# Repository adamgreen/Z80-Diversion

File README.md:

# Z80 Diversion

This project is a [Z80](https://www.zilog.com/index.php?option=com_product&Itemid=26&task=docs&businessLine=&parent_id=139&familyId=20&productId=Z84C00) based single board computer. A [RP2040 microcontroller](https://www.raspberrypi.com/documentation/microcontrollers/rp2040.html) is also included on the board. It is connected to the Z80 bus to:
* Provide the Z80 access to 64k of its 264k of SRAM.
* Allow a [Z80 compatible version of GDB](https://github.com/b-s-a/binutils-gdb) to debug the Z80 over a USB serial connection. The RP2040 is used as a hardware debugger for the Z80 much like modern JTAG or SWD probes (ie. Segger J-Link).

## Project Purpose
I want to verify some unit tests which exercise all of the instructions supported by the Z80 microprocessor. These tests can be used to verify Z80 emulation. Having the ability to also runs these tests against real Z80 hardware is desireable as it allows verifying the quality of the tests themselves. A few years ago, I did something similar for the ARMv6-M instruction tests that I wrote for my [pinkySim project](https://github.com/adamgreen/pinkySim).

## Project Progression
* The Z80, RP2040 Pico, and SN74HC165 shift register devices arrived from Digikey.
* I completed the initial schematic in KiCAD.
* I wired up an initial test version on my breadboard.
* I wrote simple proof of concept PIO and ARM code for the RP2040 to verify my hardware setup.
* I completed the initial PCB design in KiCAD.
* I ordered and received PCBs from [OSHPark](https://oshpark.com).
* I was able to download a [Z80 port of binutils/GDB](https://github.com/b-s-a/binutils-gdb) and build it on my Mac.
* I soldered up one of the PCBs and successfully tested it out with the code that I had previously developed.
* I simplified the PIO state machine code and got it running faster:
  * Can run the Z80 at 500kHz without requiring any wait cycles.
  * Can run the Z80 at faster clock rates (at least 5MHz) reliably but requires wait cycles as the RP2040 takes time to wait for the shift registers and respond to memory read/write requests.
* My [MRI core](https://github.com/adamgreen/mri) has been extended to handle debug targets which aren't just 32-bit. This will allow 64-bit in the future and 16-bit for Z80 debugging.
* The Z80 version of GDB is now able connect to the board via a RP2040 USB based serial connection to:
  * Examine and modify the Z80's 64k of RAM (which is actually a 64k global buffer on the RP2040).
  * Examine and modify the Z80's registers.
  * Single step the Z80.
  * Set up to 4 Code Breakpoints.
  * Set up to 2 Data Watchpoints
  * Z80 reset from GDB.

## Reading List
<br>
It has been around a decade since I last looked at the Z80 so I had to skim through a few Z80 references to refresh my memory of what it takes to interface this little guy to the outside world. These references included:
* [Build Your Own Z80 Computer by Steve Ciarcia](https://en.wikipedia.org/wiki/Build_Your_Own_Z80_Computer) ([Free PDF](http://www.pestingers.net/pdfs/other-computers/build-your-own-z80.pdf)).
* [Z80 CPU User Manual](https://www.zilog.com/docs/z80/UM0080.pdf)
* [Z80 Product Specification](https://www.zilog.com/docs/z80/ps0178.pdf)
* [Other Official Z80 Documents](https://www.zilog.com/index.php?option=com_product&Itemid=26&task=docs&businessLine=1&parent_id=139&familyId=20&productId=Z84C00)

I also skimmed some RP2040 documentation again as well to make sure that I had a good chance of successfully interfacing it to the Z80 before going too far down that path:
* [Raspberry Pi Pico Datasheet](https://datasheets.raspberrypi.com/pico/pico-datasheet.pdf)
* [RP2040 Datasheet](https://datasheets.raspberrypi.com/rp2040/rp2040-datasheet.pdf)

## High Level BOM
This board includes:
* A **Z80 Microprocessor** - I am using a [Z84C0020PEG](https://www.digikey.com/en/products/detail/zilog/Z84C0020PEG/928994) device since it is:
  * 20 MHz capable. I picked the fastest CMOS version of the device available. It can run at 20MHz when powered by a 5V supply but it should be able to run at a lower 3.3V (same as the RP2040) when clocked at lower frequencies (between 1 and 2.5 MHz).
  * 40-pin DIP package. Currently Digikey only has the DIP version of the 20MHz capable part in stock. I would have preferred the LQFP SMD version but it doesn't look like it will be in stock for awhile. It did make early bread boarding possible though.<br>
* A [RP2040 based Pico](https://www.digikey.com/en/products/detail/raspberry-pi/SC0915/13624793). This is connected to the Z80 bus and used to service Z80 memory requests. It also functions as a hardware debugger for the Z80. Features of the RP2040 that have been leveraged for this project include:
  * USB 1.1 controller and PHY. This allows for easy connection to a desktop/laptop. GDB can be used to program and debug the Z80 over this USB connection.
  * 264kB SRAM. 64kB of this is used to service memory read/write requests from the Z80.
  * 2MB of FLASH. Lots of room for the required firmware and storage of any ROM images that we may want to use with the Z80.
  * Programmable I/O. This was useful for interfacing with the Z80 bus without bit banging everything from the CPU.
  * Dual core Cortex-M0+ cores. Allowed dedicating a core to just servicing memory read/writes requests from the Z80. This way things like USB interrupts don't introduce random delays.
  * The Pico has the required voltage regulation to allow the board to be powered directly from USB.<br>
* 2 x [SN74HC165 8-bit shift registers](https://www.digikey.com/en/products/detail/texas-instruments/SN74HC165N/376966). This is used to latch the 16-bit address sent from the Z80 and push it into the RP2040 over 2 serial lines, one for the even bits and the other for the odd bits. I run this chip at 5V and run the serial outputs through a 3/5 voltage divider to make it compatible with the RP2040 while also allowing it to run faster. The voltage divider did end up slowing down the rise/fall times but running it at 3.3V slowed it down even more. I ended up clocking the shift registers at ~15MHz with an asymmetric clock. I hold it high for longer so that the output has time to stabilize before I sample it from the RP2040 on the falling clock edge. I would like to switch to a faster shift register in future revisions.<br>

## Programmable I/O
One of the coolest features of the RP2040 is its Programmable I/O (PIO). If you look at the block diagram of many peripherals on a microcontroller, you tend to see the same parts: inbound and outbound FIFOs, shift registers, pin I/O, and a **state machine**. The PIO has all of the same parts except that its state machine is programmable.

I leverage the programmable I/O (PIO) peripheral on the RP2040 for interfacing to the Z80 bus. I use 2 PIO state machines for this interfacing:
* The first state machine, ```AddressStateMachine```, samples the **MREQ'** / **IOREQ'** signals and shifts out the 16-bit address bits using two 8-bit shift registers:
  * It pauses if it sees **RFSH'** asserted (pulled low) since those requests are just for refreshing DRAM which can be safely ignored. Once this signal is de-asserted the state machine starts running again.
  * If it sees either of the **MREQ'** or **IOREQ'** signals go active (pulled low) then it asserts the **WAIT'** signal to let the Z80 know that it needs to wait for the RP2040 to access the requested data.
  * It will then latch the 16-bit address bits and start shifting out the address, two bits at a time.
  * Once the 16-bit address has been fully shifted in, it will be pushed to the RX FIFO for the CPU to pick up.
  * The state machine will then wait for the CPU to send back the PIO instruction that either waits on the **MREQ'** or **IOREQ'** signal being de-asserted.
  * Before executing the wait instruction it de-asserts the **WAIT'** signal to let the Z80 know that the request has been completed.
  * It then waits for the **MREQ'** or **IOREQ'** signal to be de-asserted (pulled high again) before looping around and looking for the next request. The CPU assembles the correct ```WAIT 1 GPIO n``` instruction and sends it down to the PIO state machine via its TX FIFO.
* The other state machine, ```ReadWriteStateMachine```, samples the **RD'**/**WR'** signals to determine if a read or write memory transfer is being requested by the Z80:
  * It keeps sampling the **RD'**/**WR'** signals until it sees one of them go active (pulled low).
  * The state of the **RD'**, **WR'**, **D0** - **D7** and **M1'** lines are then transferred to the CPU so that between this data and the 16-bit address from the other state machine, the CPU has enough information to perform the memory request.
  * The state machine will then wait for the CPU to send back the required response. This will include bits needed for setting **D0**-**D7** to the correct input/output state, the requested byte if a read request was made, bits to set **D0**-**D7** back to input only, and a PIO instruction that waits on the **RD'** or **WR'** signal being de-asserted.

## Current Pin Map
The PIO state machines place constraints on some signals as they will need to be mapped to consecutively numbered GPIO pins so that they can be shifted in/out as a unit. This is how the pins ended up being mapped between the RP2040 and Z80:
| RP2040 | Z80 / Shift | PIO Pin Group    | Notes |
|--------|-------------|------------------|-------|
| GP0  | Shift_In_Even | Input            | |
| GP1  | Shift_In_Odd  | Input            | |
| GP2  | MREQ'         | Input            | |
| GP3  | IOREQ'        | Input            | |
| GP4  | CLK           | Set              | |
| GP5  | Shift_Clock   | Side Set         | |
| GP6  | Shift_Latch   | Side Set         | |
| GP7  | RD'           | Input            | |
| GP8  | WR'           | Input            | |
| GP9  | D0            | Input/Output     | |
| GP10 | D1            | Input/Output     | |
| GP11 | D2            | Input/Output     | |
| GP12 | D3            | Input/Output     | |
| GP13 | D4            | Input/Output     | |
| GP14 | D5            | Input/Output     | |
| GP15 | D6            | Input/Output     | |
| GP16 | D7            | Input/Output     | |
| GP17 | M1'           | Input            | |
| GP18 | WAIT'         | Set              | 2.2kΩ Pull-Up |
| GP19 | RFSH'         | WAIT GPIO        | |
| GP20 | HALT'         | Input / Non-PIO  | |
| GP21 | NMI'          | Output / Non-PIO | 2.2kΩ Pull-Up |
| GP22 | INT'          | Output / Non-PIO | 2.2kΩ Pull-Up |
| GP26 | RESET'        | Output / Non-PIO | 3 CLK Long Pulse (3µs @ 1MHz) |
| N/C  | BUSREQ'       | Not Connected    | 2.2kΩ Pull-Up |

## Current Schematic
<br>
After wiring up this circuit on a breadboard, I found that things worked better if I made some changes to my original schematic:
* I originally thought it would work best to shift in the Z80 address bit pairs in from least significant to most significant. This results in the CPU receiving the address in the upper 16 bits and the **MREQ'** and **IOREQ'** signals values in bits 14-15. It would be nicer if the address bits were in the lower 16-bits where they can be easily masked off and used. Doing the shifts in this order required me reversing the order of the Z80 address bit connections to each of the shift registers.
* I added 0.1µF bypass capacitors to the IC power supply lines.
* I discovered that the SN74HC165 shift registers didn't have output rise and fall times that were consistent with running them at 50MHz even though I was supplying them with 5V.
  * The high resistance voltage divider I had in the original schematic to level shift this output made the problem worse.
  * Reducing the voltage divider from 55kΩ to 550Ω did shorten the rise and fall times but not enough to work at 50MHz. It does work up to 15MHz now though.
  * If I switch to SMD parts then I think there are variants of the 74*165 shift registers that can run at 3.3V and give the desired <= 10ns rise/fall times. I may try this in the future but I will just use the parts that I already have for now.
* I also wanted to test that the Z80 runs reliably at 3.3V with lower clock rates. The Z80 didn't hit any issues running NOPs at 400kHz on this breadboard setup. After I rewrote the PIO code when working with the PCB version of this circuit I was able to run it successfully at 5MHz.
* I removed the 330Ω pull-up resistor from the **CLK** signal. It was needed for TTL clocking circuits used with the older NMOS version of the Z80. I am using a CMOS version of the Z80 and driving **CLK** directly from a pin of the CMOS based RP2040 microcontroller so it isn't needed anymore.

The screenshot below shows some early traces from my logic analyzer as I began to get the Z80 successfully starting up on the breadboard above and executing NOPs supplied by the RP2040.

## PCB Design version 1.1
<br>
I completed the initial PCB design and sent it off to OSHPark to have it fabricated. It was a lot easier to work with this board than the previous mess of wires I had on my breadboard.

### Issues Discovered in Version 1.1 PCB
After soldering up the first of the version 1.1 PCBs I encountered an issue:
* When soldering the Raspberry Pi Pico to the PCB as a surface mount part there isn't enough clearance between the bottom of the USB connector on the Pico and my PCB.
  * I had to file out a groove to have it work with my USB cable on the first board I soldered up since I had already soldered the Pico down flat to the PCB surface.
  * On subsequent assemblies of this version of the PCB I will use male headers to mount the Pico as a through hole part (the footprint allows both SMD and through hole mounting). This will lift the Pico up off of the PCB to make room for the USB cable housing.
  * If I make another version of this PCB, I will align the Pico's USB connector with the edge of the PCB to eliminate this issue.

## GDB for Z80
I have past experience with using GDB and GDB debug stubs to debug Cortex-M microcontrollers. I leveraged this experience to support GDB debugging of the Z80 on this board. When I tested my ARMv6-M instruction tests on real Cortex-M hardware, I used an existing GDB debug stub and modified my test harness to pretend to be GDB so that it could place required inputs and code into RAM, setup the registers, single step over the test instruction, and then interrogate memory and registers afterwards to verify that the expected side effects occurred. I can now do the same for the Z80 using this project.

I found the following page on the web and it had lots of great information on how to use GDB with the Z80:
* [chciken's TLMBoy: Implementing the GDB Remote Serial Protocol](https://www.chciken.com/tlmboy/2022/04/03/gdb-z80.html)

### Building GDB for Z80
I have been able to download and build the same Z80 fork as @chciken:
* ```git clone https://github.com/b-s-a/binutils-gdb.git z80-gdb```
* Apply the following diff to allow the Z80 version of GDB to handle SP being set to 0x0000:
```diff
diff --git a/gdb/z80-tdep.c b/gdb/z80-tdep.c
index 641af5e06c..42f04c49f0 100644
--- a/gdb/z80-tdep.c
+++ b/gdb/z80-tdep.c
@@ -663,6 +663,7 @@ z80_frame_unwind_cache (struct frame_info *this_frame,
       /* Assume that the FP is this frame's SP but with that pushed
         stack space added back.  */
       this_base = get_frame_register_unsigned (this_frame, Z80_SP_REGNUM);
+      if (this_base == 0x0000) this_base = 1 << gdbarch_ptr_bit(gdbarch);
       sp = this_base + info->size;
       if (this_base < sp_min || sp > sp_max)
          return info;
```
* ```brew install texinfo```
* ```cd z80-gdb```
* ```mkdir build/```
* ```cd build/```
* ```LDFLAGS=-Bstatic ../configure --target=z80-unknown-elf --disable-werror --prefix=$(pwd) --exec-prefix=$(pwd)```
* ```make```
* **Note:** I don't have ```make install``` working on macOS yet. Until then, the GDB binary can be found as ```z80-gdb/build/gdb/gdb```

### Using GDB for Z80
This section shows a few snippets from an example GDB session where it is attached to my Z80 board and uses them to explain some of the debug operations supported by my firmware.

* First I will start the Z80 version of GDB that I talked about building up above. It instructs GDB to connect to a remote target using a virtual serial port, ```/dev/cu.usbmodem111301``` on my machine. GDB will give a warning about ```"No executable has been specified and target does not support determining executable automatically."``` because no .ELF file was provided. This means we have no symbols but we can still look at the low level assembly instructions, Z80 registers, and memory contents to figure out what our program is doing.
* The firmware in my board is currently written so that it loads a little test program into memory at address 0, where the Z80 starts executing upon power up, hardware reset, and ```RST 0``` commands. This sample program loads known values into all of the registers.
* The current debugger firmware also halts the Z80 when it comes out of reset, before it can even execute the first instruction at address 0x0000.
* The first command I give GDB is ```x/24i 0x0000``` This asks GDB to dump the first 24 **i**nstructions starting at address 0x0000.
  * The disassemble instruction doesn't work because it requires symbols to know where a function starts and we don't have a .ELF to provide those symbols.
  * This lets us see the contents of the test program used to load known values into the registers.
```
~/depots/Z80-Diversion$ ~/depots/z80-gdb/build/gdb/gdb -ex "set target-charset ASCII" -ex "set remotelogfile z80_mri.log" -ex "target remote /dev/cu.usbmodem111301"
GNU gdb (GDB) 10.0.50.20200317-git
Copyright (C) 2020 Free Software Foundation, Inc.
License GPLv3+: GNU GPL version 3 or later <http://gnu.org/licenses/gpl.html>
This is free software: you are free to change and redistribute it.
There is NO WARRANTY, to the extent permitted by law.
Type "show copying" and "show warranty" for details.
This GDB was configured as "--host=arm-apple-darwin22.6.0 --target=z80-unknown-elf".
Type "show configuration" for configuration details.
For bug reporting instructions, please see:
<http://www.gnu.org/software/gdb/bugs/>.
Find the GDB manual and other documentation resources online at:
    <http://www.gnu.org/software/gdb/documentation/>.

For help, type "help".
Type "apropos word" to search for commands related to "word".
Remote debugging using /dev/cu.usbmodem111301
warning: No executable has been specified and target does not support
determining executable automatically.  Try using the "file" command.
0x00000000 in ?? ()
(gdb) x/24i 0x0000
=> 0x0:	ld sp,0x0000
   0x3:	ld a,0x14
   0x5:	ld i,a
   0x7:	ld a,0x15
   0x9:	ld r,a
   0xb:	ld bc,0x0001
   0xe:	push bc
   0xf:	pop af
   0x10:	ld bc,0x0203
   0x13:	ld de,0x0405
   0x16:	ld hl,0x0607
   0x19:	ld ix,0x0809
   0x1d:	ld iy,0x0a0b
   0x21:	exx
   0x22:	ex af,af'
   0x23:	ld bc,0x0c0d
   0x26:	push bc
   0x27:	pop af
   0x28:	ld bc,0x0e0f
   0x2b:	ld de,0x1011
   0x2e:	ld hl,0x1213
   0x31:	ex af,af'
   0x32:	exx
   0x33:	jr 0x0033
```

* The next command I send to GDB is ```info reg``` to dump all of the Z80 registers at once. This version of GDB exposes all Z80 registers as 16-bit quantities so the value of an 8-bit register like A can be found in the combined 16-bit AF register.
  * It shows that the ```PC``` register is currently set to 0x0 as expected when first coming out of reset.
  * The rest of the registers will be given specific values as the test program runs and we can check these later once the program completes execution and enters the infinite loop at the end.
```
(gdb) info reg
af             0x1401              [ C ]
bc             0x1495              5269
de             0x1011              0x1011
hl             0x1213              0x1213
sp             0xffe8              0xffe8
pc             0x0                 0x0
ix             0x809               0x809
iy             0xa0b               0xa0b
af'            0x1401              [ C ]
bc'            0x203               515
de'            0x405               0x405
hl'            0x607               0x607
ir             0x0                 0
```

* I have implemented support for 4 hardware code breakpoints and 2 hardware data watchpoints.
  * Below I use the ```watch *(int*)0xfffe``` command to set a watchpoint to trigger when a 16-bit integer is written to the top slot on the stack. If we look at the disassembly of the code that was dumped above, we see that the SP is set to 0x0000 by the first instruction so the first 16-bit write will occur at 0x0000-2 which underflows to a value of 0xFFFE. The ```rwatch``` and ```awatch``` commands are also supported for watchpoints on reads or accesses (reads or writes).
  * The Z80 version of GDB considers ```short``` and ```char``` to both be 8-bit values and ```int``` to be 16-bit. That's why the stack address is cast to a ```int``` in the ```watch``` command.
  * The ```break *0x32``` command below sets a breakpoint on the ```EXX``` instruction at 0x0032.

```
(gdb) watch *(int*)0xfffe
Hardware watchpoint 1: *(int*)0xfffe
(gdb) break *0x32
warning: Unable to determine inferior's software breakpoint type: couldn't find `_break_handler' function in the executable. Will be used default software breakpoint instruction RST 0x08.
Breakpoint 2 at 0x32
```

* The next GDB command, ```disp/1i $pc```, instructs GDB to dump the current Z80 instruction when execution is halted into the debugger. This is very useful when single stepping through the code.
```
(gdb) disp/1i $pc
1: x/i $pc
=> 0x0:	ld sp,0x0000
```

* We can now use the **si** instruction to single step through the machine code, 1 instruction at a time.
  * While my debug hardware can perform a low level hardware single step, the Z80 version of GDB is written expecting this to be difficult for Z80 based debug monitors so it interprets the next Z80 instruction to be executed. It determines what address the ```PC``` register will contain after it is executed and sets a breakpoint on that address.
```
(gdb) si
0x00000003 in ?? ()
1: x/i $pc
=> 0x3:	ld a,0x14
(gdb)
0x00000005 in ?? ()
1: x/i $pc
=> 0x5:	ld i,a
```

* I now give GDB the ```c``` command to continue execution as normal (no more single stepping). This will cause it to run until we CTRL+C to force a break or a breakpoint/watchpoint is encountered.
* It first stops when the first new value of ```1``` is pushed onto the top of the stack. It should be noted that watchpoints always cause the Z80 to halt on the next instruction executed after the memory access occurred and not on the instruction which actually performed the memory read or write. For example here we see it halt on a ```POP``` instruction but it was actually the previous ```PUSH``` instruction that actually wrote the new value to the stack.
```
(gdb) c
Continuing.

Hardware watchpoint 1: *(int*)0xfffe

Old value = 0
New value = 1
0x0000000f in ?? ()
1: x/i $pc
=> 0xf:	pop af
```

* It then stops when that position on the stack is overwritten yet again.
```
(gdb) c
Continuing.

Hardware watchpoint 1: *(int*)0xfffe

Old value = 1
New value = 3085
0x00000027 in ?? ()
1: x/i $pc
=> 0x27:	pop af
```

* This time the Z80 is halted when it gets to the instruction at address 0x32, the address on which breakpoint #2 was set previously.
```
(gdb) c
Continuing.

Breakpoint 2, 0x00000032 in ?? ()
1: x/i $pc
=> 0x32:	exx
```

* If we continue execution now, the Z80 will enter an infinite loop with the ```JR 0x0033``` instruction.
* To halt the Z80 so that we can look at its current state, we need to press CTRL+C in GDB to interrupt the Z80's current execution and halt into the debugger.
* The output from GDB shows that the Z80 was executing the infinite loop at 0x33 as expected.
```
(gdb) c
Continuing.
^C
Program received signal SIGINT, Interrupt.
0x00000033 in ?? ()
1: x/i $pc
=> 0x33:	jr 0x0033
```

* At this point I send the ```info reg``` command again to look at the contents of all the Z80 registers and see that they match the values that were placed in them with the little test program dumped at the beginning of this debug session: 0x00 in A, 0x01 in F, 0x02 in B, 0x03 in C, etc.
```
(gdb) info reg
af             0x1                 [ C ]
bc             0x203               515
de             0x405               0x405
hl             0x607               0x607
sp             0x0                 0x0
pc             0x33                0x33
ix             0x809               0x809
iy             0xa0b               0xa0b
af'            0xc0d               [ C P/V F3 ]
bc'            0xe0f               3599
de'            0x1011              0x1011
hl'            0x1213              0x1213
ir             0x14f7              5367
```

* The ```dump ihex memory``` command can be used to dump a specific section of memory to a .hex file. The following snippet shows dumping all 64k of memory to a file named ```test.hex```
```
(gdb) dump ihex memory test.hex 0 0x10000
(gdb) shell ls -l *.hex
-rw-r--r--  1 foobar  staff  184333 Nov  1 02:54 test.hex
```

* Such a dump can be used to write known values into memory at a later point in time using the ```restore``` command.
```
(gdb) restore test.hex
Restoring section .sec1 (0x0 to 0x10000)
```

* The ```monitor reset``` command can be used to assert the **RESET'** pin on the Z80 to force a hardware reset.
    * Breakpoints and watchpoints set before the reset are still active after the reset. This means that you can set a breakpoint at address 0x0000 to cause the Z80 to halt as soon as it comes out of reset if you want to step through your reset code.
    * The actual reset doesn't actually occur until the next ```continue``` command is sent from GDB.
```
(gdb) break *0
Breakpoint 3 at 0x0
(gdb) monitor reset
Will reset on next continue.
(gdb) c
Continuing.

Breakpoint 3, 0x00000000 in ?? ()
```

## Next Steps
* Start using the board to validate Z80 emulation unit tests.

## Potential Future Improvements?
* Use shift registers that can shift at faster rates when run at 3.3V. This is one of the things that is most limiting the performance of the current design. The CPU cycles it takes for the RP2040's Cortex-M0 core to respond to memory requests is the other but faster addressing shifting gives the CPU even more buffer.
* The board could be made smaller and look more consistent if the Z80 and shift registers were surface mount as well.

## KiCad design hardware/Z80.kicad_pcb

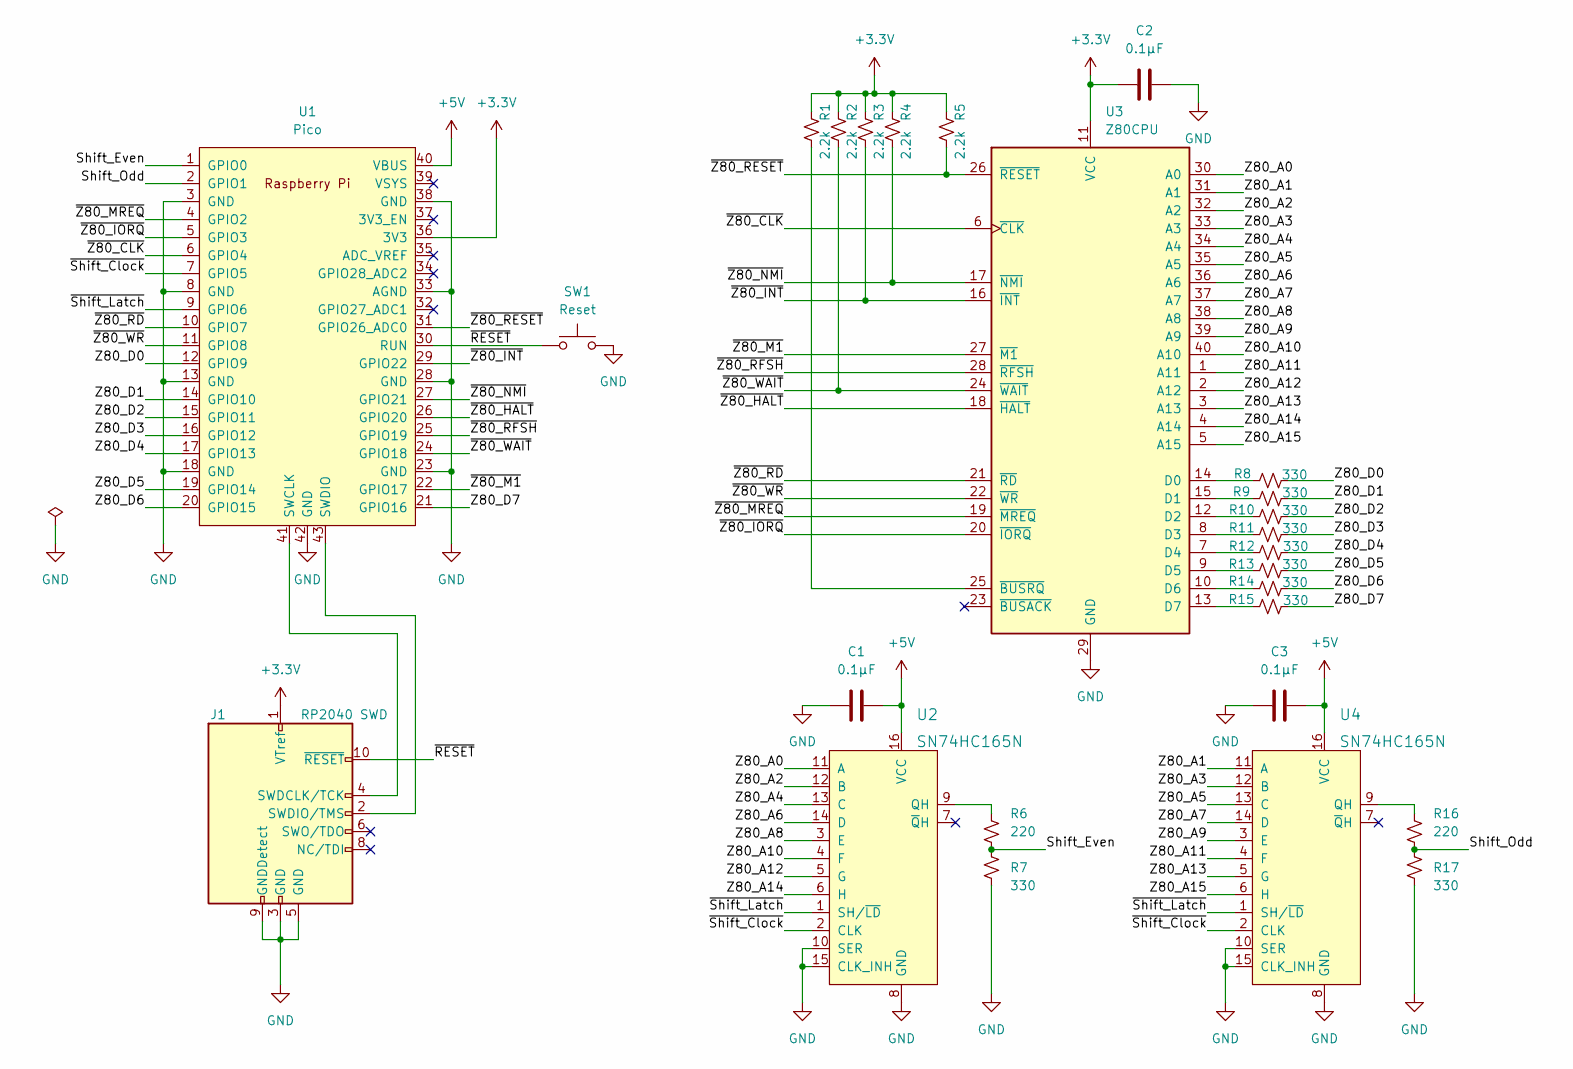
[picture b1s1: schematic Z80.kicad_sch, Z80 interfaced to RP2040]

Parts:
C1, C2, C3: 0.1µF; C_0805_2012Metric_Pad1.18x1.45mm_HandSolder
J1: RP2040 SWD; CON10_2X5_DUK_FTSH_SAI
R1, R2, R3, R4, R5: 2.2k; R_0805_2012Metric_Pad1.20x1.40mm_HandSolder
R6, R16: 220; R_0805_2012Metric_Pad1.20x1.40mm_HandSolder
R7, R8, R9, R10, R11, R12, R13, R14, R15, R17: 330; R_0805_2012Metric_Pad1.20x1.40mm_HandSolder
SW1: Reset; SW_Push_1P1T_NO_6x6mm_H9.5mm
U1: Pico; RPi_Pico_SMD_TH
U2, U4: SN74HC165N; DIP-16_W7.62mm; MPN SN74HC165N; Digi-Key_PN 296-8251-5-ND
U3: Z80CPU; DIP-40_W15.24mm

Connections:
+3.3V: C2.1, J1.1 (VTref), R1.1, R2.1, R3.1, R4.1, R5.1, U1.36 (3V3), U3.11 (VCC)
+5V: C1.2, C3.2, U1.40 (VBUS), U2.16 (VCC), U4.16 (VCC)
/Shift_Even: R6.2, R7.1, U1.1 (GPIO0)
/Shift_Odd: R16.2, R17.1, U1.2 (GPIO1)
/Z80_A0: U2.11 (A), U3.30 (A0)
/Z80_A1: U3.31 (A1), U4.11 (A)
/Z80_A2: U2.12 (B), U3.32 (A2)
/Z80_A3: U3.33 (A3), U4.12 (B)
/Z80_A4: U2.13 (C), U3.34 (A4)
/Z80_A5: U3.35 (A5), U4.13 (C)
/Z80_A6: U2.14 (D), U3.36 (A6)
/Z80_A7: U3.37 (A7), U4.14 (D)
/Z80_A8: U2.3 (E), U3.38 (A8)
/Z80_A9: U3.39 (A9), U4.3 (E)
/Z80_A10: U2.4 (F), U3.40 (A10)
/Z80_A11: U3.1 (A11), U4.4 (F)
/Z80_A12: U2.5 (G), U3.2 (A12)
/Z80_A13: U3.3 (A13), U4.5 (G)
/Z80_A14: U2.6 (H), U3.4 (A14)
/Z80_A15: U3.5 (A15), U4.6 (H)
/Z80_D0: R8.2, U1.12 (GPIO9)
/Z80_D1: R9.2, U1.14 (GPIO10)
/Z80_D2: R10.2, U1.15 (GPIO11)
/Z80_D3: R11.2, U1.16 (GPIO12)
/Z80_D4: R12.2, U1.17 (GPIO13)
/Z80_D5: R13.2, U1.19 (GPIO14)
/Z80_D6: R14.2, U1.20 (GPIO15)
/Z80_D7: R15.2, U1.21 (GPIO16)
/~RESET: J1.10 (~RESET), SW1.1, U1.30 (RUN)
/~Shift_Clock: U1.7 (GPIO5), U2.2 (CLK), U4.2 (CLK)
/~Shift_Latch: U1.9 (GPIO6), U2.1 (SH/~LD), U4.1 (SH/~LD)
/~Z80_CLK: U1.6 (GPIO4), U3.6 (~CLK)
/~Z80_HALT: U1.26 (GPIO20), U3.18 (~HALT)
/~Z80_INT: R3.2, U1.29 (GPIO22), U3.16 (~INT)
/~Z80_IORQ: U1.5 (GPIO3), U3.20 (~IORQ)
/~Z80_M1: U1.22 (GPIO17), U3.27 (~M1)
/~Z80_MREQ: U1.4 (GPIO2), U3.19 (~MREQ)
/~Z80_NMI: R4.2, U1.27 (GPIO21), U3.17 (~NMI)
/~Z80_RD: U1.10 (GPIO7), U3.21 (~RD)
/~Z80_RESET: R5.2, U1.31 (GPIO26_ADC0), U3.26 (~RESET)
/~Z80_RFSH: U1.25 (GPIO19), U3.28 (~RFSH)
/~Z80_WAIT: R2.2, U1.24 (GPIO18), U3.24 (~WAIT)
/~Z80_WR: U1.11 (GPIO8), U3.22 (~WR)
GND: C1.1, C2.2, C3.1, J1.3 (GND), J1.5 (GND), J1.9 (GNDDetect), R7.2, R17.2, SW1.2, U1.3 (GND), U1.8 (GND), U1.13 (GND), U1.18 (GND), U1.23 (GND), U1.28 (GND), U1.33 (AGND), U1.38 (GND), U1.42 (GND), U2.8 (GND), U2.10 (SER), U2.15 (CLK_INH), U3.29 (GND), U4.8 (GND), U4.10 (SER), U4.15 (CLK_INH)
unnamed: J1.2 (SWDIO/TMS), U1.43 (SWDIO)
unnamed: J1.4 (SWDCLK/TCK), U1.41 (SWCLK)
unnamed: R1.2, U3.25 (~BUSRQ)
unnamed: R6.1, U2.9 (QH)
unnamed: R8.1, U3.14 (D0)
unnamed: R9.1, U3.15 (D1)
unnamed: R10.1, U3.12 (D2)
unnamed: R11.1, U3.8 (D3)
unnamed: R12.1, U3.7 (D4)
unnamed: R13.1, U3.9 (D5)
unnamed: R14.1, U3.10 (D6)
unnamed: R15.1, U3.13 (D7)
unnamed: R16.1, U4.9 (QH)

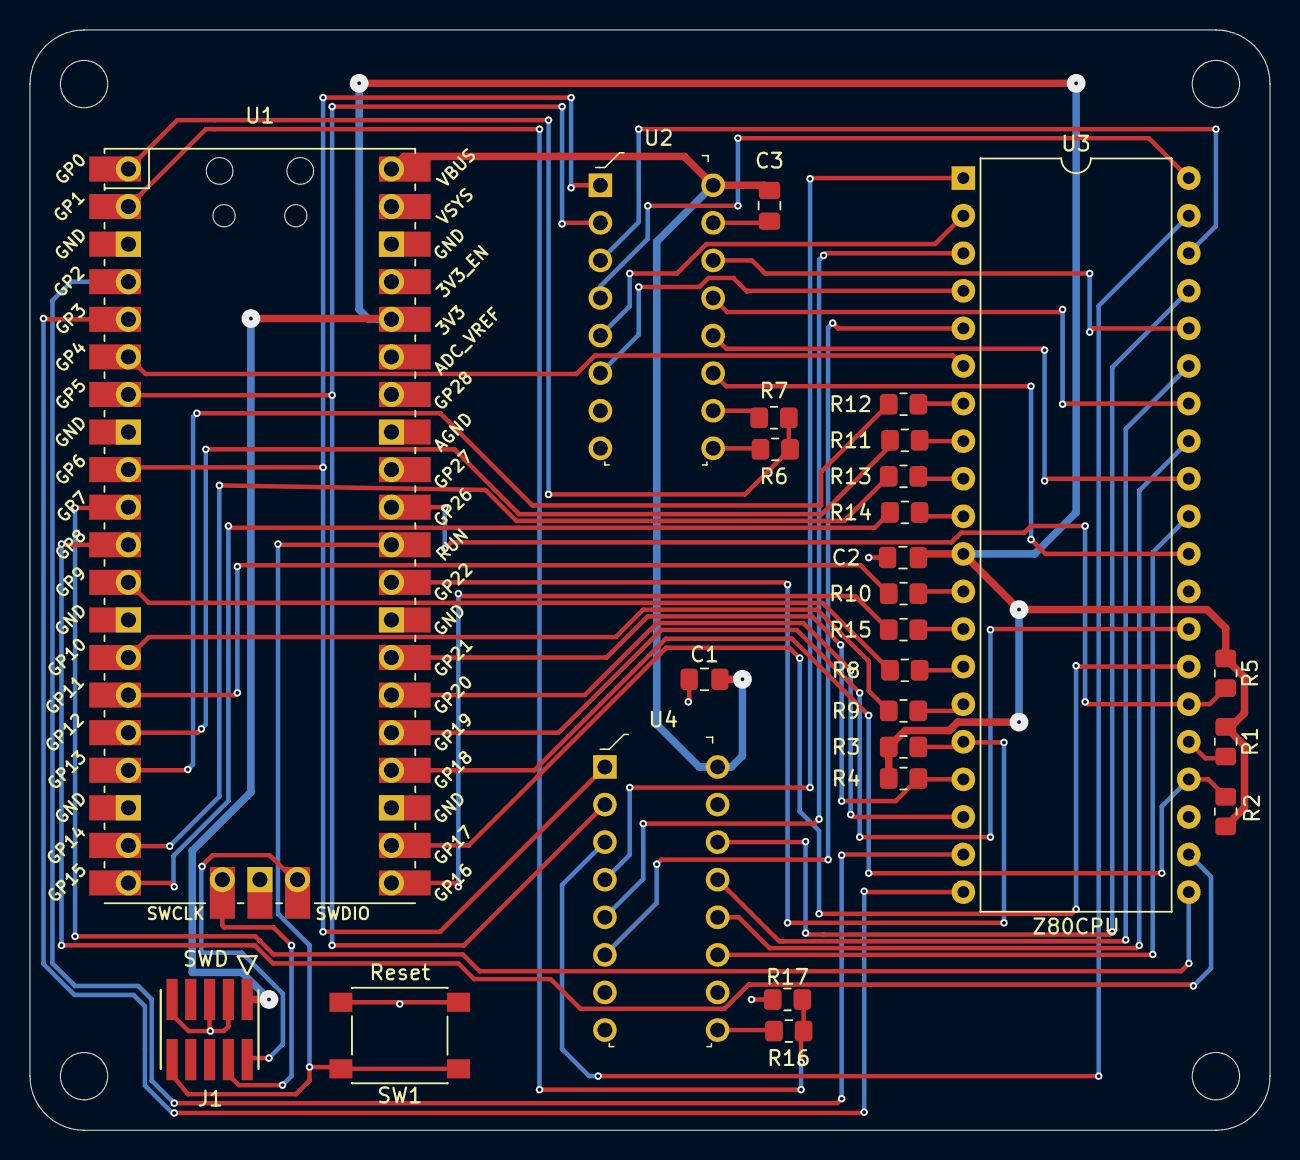
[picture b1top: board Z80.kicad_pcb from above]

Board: 2 copper layers, 83.8 x 74.4 mm, 26 parts (0 on the bottom side), 57 nets.

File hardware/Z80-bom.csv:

"Source:","/Users/adamgreen/depots/Z80-Diversion/hardware/Z80.kicad_sch"
"Date:","Friday, October 06, 2023 at 06:04:24 PM"
"Tool:","Eeschema (6.0.7-1)-1"
"Generator:","/Applications/KiCad/KiCad.app/Contents/SharedSupport/plugins/bom_csv_grouped_by_value.py"
"Component Count:","26"

"Individual Components:"

"Item","Qty","Reference(s)","Value","LibPart","Footprint","Datasheet","Category","DK_Datasheet_Link","DK_Detail_Page","Description","Digi-Key_PN","Family","MPN","Manufacturer","Status"
"","","C1","0.1µF","Device:C","Capacitor_SMD:C_0805_2012Metric_Pad1.18x1.45mm_HandSolder","~","","","","","","","","",""
"","","C2","0.1µF","Device:C","Capacitor_SMD:C_0805_2012Metric_Pad1.18x1.45mm_HandSolder","~","","","","","","","","",""
"","","C3","0.1µF","Device:C","Capacitor_SMD:C_0805_2012Metric_Pad1.18x1.45mm_HandSolder","~","","","","","","","","",""
"","","J1","RP2040 SWD","Connector:Conn_ARM_JTAG_SWD_10","SWD_footprints:CON10_2X5_DUK_FTSH_SAI","http://infocenter.arm.com/help/topic/com.arm.doc.ddi0314h/DD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","","","","","","","","",""
"","","R1","2.2k","Device:R_Small_US","Resistor_SMD:R_0805_2012Metric_Pad1.20x1.40mm_HandSolder","~","","","","","","","","",""
"","","R2","2.2k","Device:R_Small_US","Resistor_SMD:R_0805_2012Metric_Pad1.20x1.40mm_HandSolder","~","","","","","","","","",""
"","","R3","2.2k","Device:R_Small_US","Resistor_SMD:R_0805_2012Metric_Pad1.20x1.40mm_HandSolder","~","","","","","","","","",""
"","","R4","2.2k","Device:R_Small_US","Resistor_SMD:R_0805_2012Metric_Pad1.20x1.40mm_HandSolder","~","","","","","","","","",""
"","","R5","2.2k","Device:R_Small_US","Resistor_SMD:R_0805_2012Metric_Pad1.20x1.40mm_HandSolder","~","","","","","","","","",""
"","","R6","220","Device:R_Small_US","Resistor_SMD:R_0805_2012Metric_Pad1.20x1.40mm_HandSolder","~","","","","","","","","",""
"","","R7","330","Device:R_Small_US","Resistor_SMD:R_0805_2012Metric_Pad1.20x1.40mm_HandSolder","~","","","","","","","","",""
"","","R8","330","Device:R_Small_US","Resistor_SMD:R_0805_2012Metric_Pad1.20x1.40mm_HandSolder","~","","","","","","","","",""
"","","R9","330","Device:R_Small_US","Resistor_SMD:R_0805_2012Metric_Pad1.20x1.40mm_HandSolder","~","","","","","","","","",""
"","","R10","330","Device:R_Small_US","Resistor_SMD:R_0805_2012Metric_Pad1.20x1.40mm_HandSolder","~","","","","","","","","",""
"","","R11","330","Device:R_Small_US","Resistor_SMD:R_0805_2012Metric_Pad1.20x1.40mm_HandSolder","~","","","","","","","","",""
"","","R12","330","Device:R_Small_US","Resistor_SMD:R_0805_2012Metric_Pad1.20x1.40mm_HandSolder","~","","","","","","","","",""
"","","R13","330","Device:R_Small_US","Resistor_SMD:R_0805_2012Metric_Pad1.20x1.40mm_HandSolder","~","","","","","","","","",""
"","","R14","330","Device:R_Small_US","Resistor_SMD:R_0805_2012Metric_Pad1.20x1.40mm_HandSolder","~","","","","","","","","",""
"","","R15","330","Device:R_Small_US","Resistor_SMD:R_0805_2012Metric_Pad1.20x1.40mm_HandSolder","~","","","","","","","","",""
"","","R16","220","Device:R_Small_US","Resistor_SMD:R_0805_2012Metric_Pad1.20x1.40mm_HandSolder","~","","","","","","","","",""
"","","R17","330","Device:R_Small_US","Resistor_SMD:R_0805_2012Metric_Pad1.20x1.40mm_HandSolder","~","","","","","","","","",""
"","","SW1","Reset","Switch:SW_Push","Button_Switch_SMD:SW_Push_1P1T_NO_6x6mm_H9.5mm","~","","","","","","","","",""
"","","U1","Pico","RPi_Pico:Pico","RPi_Pico:RPi_Pico_SMD_TH","","","","","","","","","",""
"","","U2","SN74HC165N","dk_Logic-Shift-Registers:SN74HC165N","digikey-footprints:DIP-16_W7.62mm","http://www.ti.com/general/docs/suppproductinfo.tsp?distId=10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","Integrated Circuits (ICs)","http://www.ti.com/general/docs/suppproductinfo.tsp?distId=10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","/product-detail/en/texas-instruments/SN74HC165N/296-8251-5-ND/376966","IC 8-BIT SHIFT REGISTER 16-DIP","296-8251-5-ND","Logic - Shift Registers","SN74HC165N","Texas Instruments","Active"
"","","U3","Z80CPU","CPU:Z80CPU","Package_DIP:DIP-40_W15.24mm","www.zilog.com/manage_directlink.php?filepath=docs/z80/um0080","","","","","","","","",""
"","","U4","SN74HC165N","dk_Logic-Shift-Registers:SN74HC165N","digikey-footprints:DIP-16_W7.62mm","http://www.ti.com/general/docs/suppproductinfo.tsp?distId=10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","Integrated Circuits (ICs)","http://www.ti.com/general/docs/suppproductinfo.tsp?distId=10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","/product-detail/en/texas-instruments/SN74HC165N/296-8251-5-ND/376966","IC 8-BIT SHIFT REGISTER 16-DIP","296-8251-5-ND","Logic - Shift Registers","SN74HC165N","Texas Instruments","Active"



"Collated Components:"

"Item","Qty","Reference(s)","Value","LibPart","Footprint","Datasheet","Category","DK_Datasheet_Link","DK_Detail_Page","Description","Digi-Key_PN","Family","MPN","Manufacturer","Status"
"1","3","C1, C2, C3","0.1µF","Device:C","Capacitor_SMD:C_0805_2012Metric_Pad1.18x1.45mm_HandSolder","~","","","","","","","","",""
"2","1","J1","RP2040 SWD","Connector:Conn_ARM_JTAG_SWD_10","SWD_footprints:CON10_2X5_DUK_FTSH_SAI","http://infocenter.arm.com/help/topic/com.arm.doc.ddi0314h/DD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","","","","","","","","",""
"3","5","R1, R2, R3, R4, R5","2.2k","Device:R_Small_US","Resistor_SMD:R_0805_2012Metric_Pad1.20x1.40mm_HandSolder","~","","","","","","","","",""
"4","2","R6, R16","220","Device:R_Small_US","Resistor_SMD:R_0805_2012Metric_Pad1.20x1.40mm_HandSolder","~","","","","","","","","",""
"5","10","R7, R8, R9, R10, R11, R12, R13, R14, R15, R17","330","Device:R_Small_US","Resistor_SMD:R_0805_2012Metric_Pad1.20x1.40mm_HandSolder","~","","","","","","","","",""
"6","1","SW1","Reset","Switch:SW_Push","Button_Switch_SMD:SW_Push_1P1T_NO_6x6mm_H9.5mm","~","","","","","","","","",""
"7","1","U1","Pico","RPi_Pico:Pico","RPi_Pico:RPi_Pico_SMD_TH","","","","","","","","","",""
"8","2","U2, U4","SN74HC165N","dk_Logic-Shift-Registers:SN74HC165N","digikey-footprints:DIP-16_W7.62mm","http://www.ti.com/general/docs/suppproductinfo.tsp?distId=10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","Integrated Circuits (ICs)","http://www.ti.com/general/docs/suppproductinfo.tsp?distId=10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","/product-detail/en/texas-instruments/SN74HC165N/296-8251-5-ND/376966","IC 8-BIT SHIFT REGISTER 16-DIP","296-8251-5-ND","Logic - Shift Registers","SN74HC165N","Texas Instruments","Active"
"9","1","U3","Z80CPU","CPU:Z80CPU","Package_DIP:DIP-40_W15.24mm","www.zilog.com/manage_directlink.php?filepath=docs/z80/um0080","","","","","","","","",""

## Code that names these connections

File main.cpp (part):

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

// Z80 bus pin definitions.
static const uint32_t Z80_MREQ_PIN = 2;
static const uint32_t Z80_IOREQ_PIN = 3;
static const uint32_t Z80_CLK_PIN = 4;
static const uint32_t Z80_RD_PIN = 7;
static const uint32_t Z80_WR_PIN = 8;
static const uint32_t Z80_D0_PIN = 9;
static const uint32_t Z80_D1_PIN = 10;
static const uint32_t Z80_D2_PIN = 11;
static const uint32_t Z80_D3_PIN = 12;
static const uint32_t Z80_D4_PIN = 13;
static const uint32_t Z80_D5_PIN = 14;
static const uint32_t Z80_D6_PIN = 15;
static const uint32_t Z80_D7_PIN = 16;
static const uint32_t Z80_M1_PIN = 17;
static const uint32_t Z80_WAIT_PIN = 18;
static const uint32_t Z80_RFSH_PIN = 19;
static const uint32_t Z80_HALT_PIN = 20;
static const uint32_t Z80_NMI_PIN = 21;
static const uint32_t Z80_INT_PIN = 22;
static const uint32_t Z80_RESET_PIN = 26;

// Shift register pin definitions.
static const uint32_t SHIFT_EVEN_PIN = 0;
static const uint32_t SHIFT_ODD_PIN = 1;
static const uint32_t SHIFT_CLOCK_PIN = 5;
static const uint32_t SHIFT_LATCH_PIN = 6;

// The frequency at which the Z80 should be clocked.
static const uint32_t Z80_FREQUENCY = 500000;
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
    // Configure the PIO state machines to manage the Z80 bus and let the RP2040 core know when memory or I/O requests
    // have been made by the Z80 so that the RP2040 core can handle them.
    bool result = g_z80Bus.init(Z80_FREQUENCY, Z80_RESET_PIN, Z80_CLK_PIN,
                                Z80_MREQ_PIN, Z80_IOREQ_PIN, Z80_RD_PIN, Z80_WR_PIN,
                                Z80_D0_PIN, Z80_D1_PIN, Z80_D2_PIN, Z80_D3_PIN,
                                Z80_D4_PIN, Z80_D5_PIN, Z80_D6_PIN, Z80_D7_PIN,
                                Z80_M1_PIN, Z80_WAIT_PIN, Z80_RFSH_PIN, Z80_HALT_PIN,
                                SHIFT_CLOCK_PIN, SHIFT_LATCH_PIN, SHIFT_EVEN_PIN, SHIFT_ODD_PIN);
    assert ( result );
    (void)result;

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
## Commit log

2023-08-30 Update README
    Added notes about pull-ups from what I saw in the "Build Your Own Z80
    Computer" book by Steve Ciarcia.
2023-09-02 Update README
    The parts have arrived from Digikey. I have added photos of the 3 main
    BOM items now that I have them in my possession.
2023-09-02 Added initial schematic
    This should be enough to get me started on the breadboarding portion of
    this project.
2023-09-04 Add link to free PDF of Z80 book
2023-09-15 Initial firmware commit
    This is a simple little program that makes sure that the RP2040 and its
    PIO hardware can be used to clock the Z80 microprocessor and satisfy
    its memory requests. It runs a simple Z80 program that increments a
    16-bit counter in a loop and verifies that this counter is incremented
    as expected.
    * Updated README to cover the latest developments on this project.
2023-09-15 Update schematic
2023-09-16 Initial PCB design
    * Designed version 1.1 of the PCB and sent it off to OSHPark to have it
    fabricated.
    * Fixed a missing connection between 3.3V and a bunch of Z80 pull-ups
    that I had in my schematic that I didn't notice until I was working
    on the PCB.
    * Updated README with the latest project progression.
2023-09-17 Update README
    I have some new ideas on next steps.
2023-09-19 Update README
    * Got Z80 fork of binutils and GDB building on my Mac.
    * OSHPark has started making my boards.
2023-10-07 Update README
    Added notes after receiving and soldering up version 1.1 of the PCBs.
2023-10-11 Rewrite of PIO code
    I rewrote both the PIO state machines to be more async in nature. Now
    they both just look for edges in signals such as MREQ', IOREQ', RD',
    and WR' while ignoring the Z80 clock signal itself. This greatly
    simplified the first state machine's code since it no longer has to
    generate the Z80 clock while also checking for memory requests and
    shifting out the address bits.
2023-10-11 AddressStateMachine should assert WAIT'
    Previously I was setting the Z80 WAIT' signal from the
    ReadWriteStateMachine but for writes this meant that I asserted WAIT'
    one Z80 clock cycle too late and this would result in the Z80
    de-asserting MREQ' and WR' while the Cortex-M0+ core was still
    processing the write.
    Now I do it in the AddressStateMachine which means that WAIT' can be
2023-10-11 Add more tests
    Still running the same simple 16-bit counter incrementing program on
    the Z80 but now the C++ code on the RP2040 verifies that every Z80
    memory access is as expected:
    * Read or Write access.
    * Address of access.
    * M1' state of access.
2023-10-11 Run AddressStateMachine 4x faster
    I added 4x delay to the shift register clocking instructions themselves
    and then run the state machine 4x faster to reduce the time between
    MREQ'/IOREQ' being assserted and the start of the address shifting.
    When running at 700kHz, this shaves off 130µs.
    I tried 8x but this generates too fast of a state machine frequency so
    I used 4x instead. This will break at Z80 frequencies above 976kHz but
2023-10-12 Remove redundant shift register clock pulse
    The way the PIO code was written before, a full 8 clock cycles were
    sent to the pair of shift registers but only 7 are required since the
    first bit is ready at the time of latching. It did require adding 2
    more PIO instructions to generate these fewer clock pulses though.
    When running the Z80 at 750kHz this gives an additional 112ns between
    the time the shifts complete and the next Z80 clock falling edge, the
2023-10-12 Use asymmetric shift register clock
    The shift register has a maximum clock frequency of 50MHz when run at
    5.0V so it can go faster than the 12.5MHz limit that I hit because of
    the slow rise/fall times on its outputs. It is only the high portion of
    the clock that accounts for this rise/fall time before it is sampled by
    the PIO on the falling edge. The low portion of the clock can be much
    shorter and not cause any problem. That means if I run the clock
2023-10-12 Handle changing RFSH' pin assignment
    Previously the RFSH' pin assignment to GPIO 19 was hardcoded in
    the z80_bus.pio assembly language file. rfshPin is provided as a
    parameter to Z80_Bus::initAddressStateMachine() and this commit
    modifies it to overwrite the machine code for this instruction with
    the correct "wait 1 gpio rfshPin side 0b10". This makes it easier to
    change in the future like the rest of the pins.
2023-10-12 Some code cleanup
    * Remove ClockStateMachine and just use PWM for clocking the Z80
    instead. This saves 2 PIO instructions.
    * Renamed the PIO assembly language routines for the 2 remaining
    state machines to match the names I use elsewhere in the code.
    * Refactored the Z80_Bus::Request structure to use 16-bits for the
    address and 8-bits for the value members.
2023-10-23 Added debugger support
    GDB can now attach over the USB Serial port to debug the Z80. It
    supports:
    * Memory read/writes
    * Register reads/writes
    * CTRL+C halting
    * Single stepping
2023-10-23 Update README
    Just cleaned it up a bit and added notes now that the first version of
    the PCB and firmware are up and running as needed.
2023-10-31 Upgrade PCB design to KiCAD 7
2023-10-31 GDB can now handle SP being set to 0x0000
    - Added the diff for my GDB SP fix to the README.
    - Updated test program in main.cpp to initialize SP to 0x0000 as I had
    originally written it now that it doesn't cause problems for GDB.
    - Added explicit carriage return to printf() statements now that I have
    turned off end of line translation so that it doesn't corrupt packets
    sent to GDB.
2023-11-01 Add sample GDB session to README
    This will help me to remember what I can and can't do with this debugger
    setup in the future.
2023-11-03 Add "monitor reset" support
    Can now use the "monitor reset" command in GDB to perform a hardware
    reset on the Z80.
    * The Z80Bus class already had code which would reset the Z80 as part of
    of its existing init() method. To perform a later reset all I had to
    do was call uninit() and then init() again. This resets the PIO state
    machines and the Z80 device as expected.
2023-11-04 Don't modify stack when halting Z80 into debugger
    Previously the halting process would use the Z80's actual stack to store
    the registers for grabbing the Z80 context. Now it is redirected to
    g_fakeStack instead. This means that the Z80's RAM isn't polluted with
    these register values anymore. This might make it easier to debug stack
    corruptions or situations where a small stack is used and pushing these
    register values on the stack might overwrite application data or code.

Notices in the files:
main.cpp:
Copyright 2023 Adam Green (https://github.com/adamgreen/)
Licensed under the Apache License, Version 2.0 (the "License");
